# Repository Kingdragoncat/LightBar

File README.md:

# LightBar

simple extendable light bar meant to be mounted to whatever project you want. just chain em together and go

## what is this thing

its a PCB with 21 WS2812B addressable LEDs on it. theres connectors on both ends so you can daisy chain multiple bars together. each LED has its own 100nF bypass cap. theres also mounting holes on each end so you can screw it down to stuff

## pcb layout

## schematic

## specs

- 21x WS2812B addressable RGB LEDs
- 5V power
- data in/out connectors on both ends for daisy chaining
- 100nF decoupling cap per LED
- 47uF bulk cap on the power rail
- 330 ohm resistors on data lines
- mounting holes on both ends
- designed in KiCad

## wiring

hook up 5V, GND, and data to the input connector and youre good. if you want more bars just connect the output of one to the input of the next

## BOM

| Ref | Qty | Value | Package | Description | Unit Price | Subtotal | Link |
|-----|-----|-------|---------|-------------|-----------|----------|------|
| D1-D21 | 21 | WS2812B | 5050 PLCC4 | Addressable RGB LED | $0.11 | $2.31 | [LCSC](https://www.lcsc.com/product-detail/Light-Emitting-Diodes-LED_Worldsemi-WS2812B-B-W_C2761795.html) |
| C1-C21 | 21 | 100nF | 1206 | Ceramic decoupling cap | $0.03 | $0.63 | [LCSC](https://www.lcsc.com/product-detail/Walsin-1206B104K500CT_C93194.html) |
| C22 | 1 | 47uF | 1210 | Ceramic bulk cap | $0.25 | $0.25 | [LCSC](https://www.lcsc.com/product-detail/TORCH-CT4G-1210-X5R-16V-47uF-K_C2960960.html) |
| R1, R2 | 2 | 330Ω | 1206 | SMD resistor | $0.01 | $0.02 | [LCSC](https://www.lcsc.com/search?q=1206%20330%20ohm) |
| J1, J2 | 2 | Conn_01x03 | JST XH 3-pin | Through-hole connector (S3B-XH-A) | $0.08 | $0.16 | [LCSC](https://www.lcsc.com/product-detail/JST-S3B-XH-A-LF-SN_C157928.html) |

**total: 47 parts — ~$3.37**

## license

do whatever you want with it honestly

---

made by Jonah Novoseller (Kingdragoncat)

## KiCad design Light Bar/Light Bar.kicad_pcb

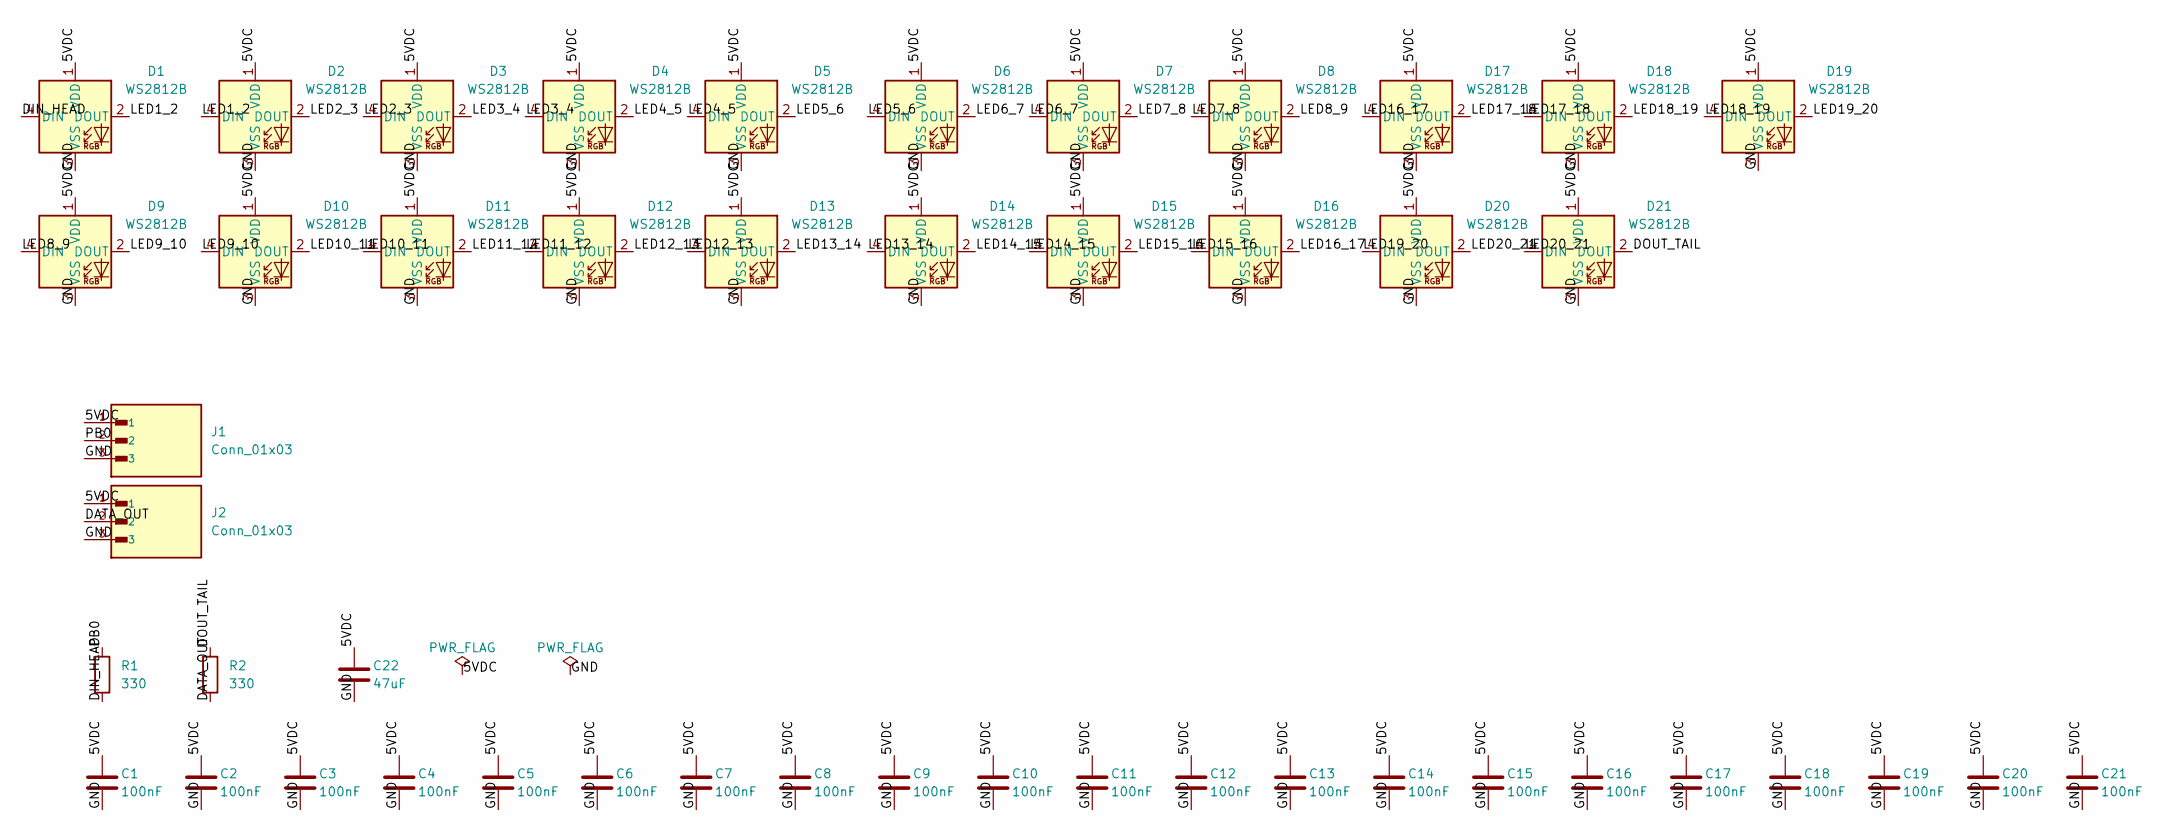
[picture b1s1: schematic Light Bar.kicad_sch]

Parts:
C1, C2, C3, C4, C5, C6, C7, C8, C9, C10, C11, C12, C13, C14, C15, C16, C17, C18, C19, C20, C21: 100nF; C_1206_3216Metric
C22: 47uF; C_1210_3225Metric
D1, D2, D3, D4, D5, D6, D7, D8, D9, D10, D11, D12, D13, D14, D15, D16, D17, D18, D19, D20, D21: WS2812B; LED_WS2812B_PLCC4_5.0x5.0mm_P3.2mm
J1, J2: Conn_01x03; JST_XH_S3B-XH-A_1x03_P2.50mm_Horizontal
R1, R2: 330; R_1206_3216Metric

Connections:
/5VDC: C1.1, C2.1, C3.1, C4.1, C5.1, C6.1, C7.1, C8.1, C9.1, C10.1, C11.1, C12.1, C13.1, C14.1, C15.1, C16.1, C17.1, C18.1, C19.1, C20.1, C21.1, C22.1, D1.1 (VDD), D2.1 (VDD), D3.1 (VDD), D4.1 (VDD), D5.1 (VDD), D6.1 (VDD), D7.1 (VDD), D8.1 (VDD), D9.1 (VDD), D10.1 (VDD), D11.1 (VDD), D12.1 (VDD), D13.1 (VDD), D14.1 (VDD), D15.1 (VDD), D16.1 (VDD), D17.1 (VDD), D18.1 (VDD), D19.1 (VDD), D20.1 (VDD), D21.1 (VDD), J1.1, J2.1
/DATA_OUT: J2.2, R2.2
/DIN_HEAD: D1.4 (DIN), R1.2
/DOUT_TAIL: D21.2 (DOUT), R2.1
/LED1_2: D1.2 (DOUT), D2.4 (DIN)
/LED2_3: D2.2 (DOUT), D3.4 (DIN)
/LED3_4: D3.2 (DOUT), D4.4 (DIN)
/LED4_5: D4.2 (DOUT), D5.4 (DIN)
/LED5_6: D5.2 (DOUT), D6.4 (DIN)
/LED6_7: D6.2 (DOUT), D7.4 (DIN)
/LED7_8: D7.2 (DOUT), D8.4 (DIN)
/LED8_9: D8.2 (DOUT), D9.4 (DIN)
/LED9_10: D9.2 (DOUT), D10.4 (DIN)
/LED10_11: D10.2 (DOUT), D11.4 (DIN)
/LED11_12: D11.2 (DOUT), D12.4 (DIN)
/LED12_13: D12.2 (DOUT), D13.4 (DIN)
/LED13_14: D13.2 (DOUT), D14.4 (DIN)
/LED14_15: D14.2 (DOUT), D15.4 (DIN)
/LED15_16: D15.2 (DOUT), D16.4 (DIN)
/LED16_17: D16.2 (DOUT), D17.4 (DIN)
/LED17_18: D17.2 (DOUT), D18.4 (DIN)
/LED18_19: D18.2 (DOUT), D19.4 (DIN)
/LED19_20: D19.2 (DOUT), D20.4 (DIN)
/LED20_21: D20.2 (DOUT), D21.4 (DIN)
/PB0: J1.2, R1.1
GND: C1.2, C2.2, C3.2, C4.2, C5.2, C6.2, C7.2, C8.2, C9.2, C10.2, C11.2, C12.2, C13.2, C14.2, C15.2, C16.2, C17.2, C18.2, C19.2, C20.2, C21.2, C22.2, D1.3 (VSS), D2.3 (VSS), D3.3 (VSS), D4.3 (VSS), D5.3 (VSS), D6.3 (VSS), D7.3 (VSS), D8.3 (VSS), D9.3 (VSS), D10.3 (VSS), D11.3 (VSS), D12.3 (VSS), D13.3 (VSS), D14.3 (VSS), D15.3 (VSS), D16.3 (VSS), D17.3 (VSS), D18.3 (VSS), D19.3 (VSS), D20.3 (VSS), D21.3 (VSS), J1.3, J2.3

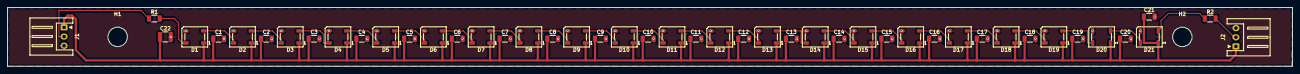
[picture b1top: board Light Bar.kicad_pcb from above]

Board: 2 copper layers, 350.0 x 16.0 mm, 49 parts (0 on the bottom side), 26 nets.

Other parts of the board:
H1, H2: MountingHole_5.3mm_M5

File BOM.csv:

Reference,Qty,Value,Package,Description,Link
"D1-D21",21,WS2812B,5050 PLCC4,Addressable RGB LED,https://www.lcsc.com/product-detail/Light-Emitting-Diodes-LE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
"C1-C21",21,100nF,1206,Ceramic decoupling capacitor,https://www.lcsc.com/product-detail/Walsin-1206B104K500CT_C9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
"C22",1,47uF,1210,Ceramic bulk capacitor,https://www.lcsc.com/product-detail/TORCH-CT4G-1210-X5R-16V-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
"R1, R2",2,330,1206,SMD resistor,https://www.lcsc.com/search?q=1206%20330%20ohm
"J1, J2",2,Conn_01x03,JST XH 3-pin,Through-hole right angle connector (S3B-XH-A),https://www.lcsc.com/product-detail/JST-S3B-XH-A-LF-SN_C157928.html
